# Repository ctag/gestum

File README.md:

# Space Sensei (せんせい)

*Firmware which automatically pairs Bosch SensorTec BNO055 library to any number of sensors and shuttles quaternions to a host computer.*

## Firmware setup

### Serial settings

38400 baud, 8N1

## TLV Packets

TLV (Type-Length-Value-Checksum) is used to minimize data required to send quaternions to host computer.

### Format

* Type - 1 byte opcode (e.g. 0x0C)
* Length - 1 byte unsigned int length of value field.
	* Note - Entire packet is always 'length + 3'
* Value - Raw bytearray.
* Checksum - 1 byte. Validates data integrity.https://68.media.tumblr.com/avatar_ef804b42fa43_128.png
	* Type + Length + [Value1 + Value2 + ValueN] + Checksum = 0x00

### Notes

* Not using preamble/postamble because timeout takes care of synchronization.
	* Timeout is ~30ms. So if comms go down, wait a while and try again.
* Not parsed without length byte.
	* Minimum packet length is 3 bytes.

### Opcodes

Even opcodes are master->mcu. Odd ones are mcu->master.

* 0x02: Heartbeat request (ping)
	* No Value field.
	* Packet: 0x0200FE
* 0x03: Heartbeat response (pong)
	* No Value field.
	* Packet: 0x0300FD
* 0x04: Request System State
	* No Value field.
	* Packet: 0x0400FC
* 0x05: Return System State
	* Value field is 1-2 uint8. 
	* See System state section below.
* 0x06: Request BNO count
	* No Value field.
	* Packet: 0x0600FA
* 0x07: Return BNO count
	* Value field is one uint8
* 0x08: Request BNO Calibration Status
	* Value field is uint8 index of BNO. Must be less than BNO count.
* 0x09: Return BNO Calibration Status
	* Value field is 4 uint8.
	* In order: accel, gyro, mag, sys.
	* Page 48 of datasheet for more.
* 0x0A: Request BNO Quaternion
	* Value field is BNO index.
* 0x0B: Return BNO Quaternion
	* Value field is quaternion. 4 bytes.
* 0xAA: Generic system error
* 0xAB: Generic system error
* 0xAC: Checksum error
* 0xAD: Checksum error
* 0xAE: Timeout with partial packet
* 0xAF: Timeout with partial packet

### System state

Sent as a uint8. Constructed such that any nonzero number indicates a problem (except bootup, which just means wait a bit).

* 0 - Everything's good
* 1 - Bootup (everything's still good)
* 2 - No BNOs detected during scan. Connect them and reboot system.
* 3 - Error initializing BNO. Cycle power to system. Should send erroneous BNO #.

## BNO055

We're using Bosch's BNO055 9-axis fusion IMU. It kinda sucks, and looks like this:

It has a [datasheet](doc/datasheet.pdf), and [C microcontroller library](https://github.com/BoschSensortec/BNO055_driver), with a [3rd party guide](doc/IntegrateBNO055.pdf) to help you integrate the library to your project.

### Bootup

On boot the BNO automatically falls into calibration mode. The space sensei firmware will wait until the minimum (maybe) calibration is met. Then it will proceed to normal operation.

On the debugging hardware, an LED is yellow during calibration, then switches to green for normal operation.

For NDEF mode (which we're using) the most basic calibration required is magnotometer (rotate sensor 360 like a compass).

### Calibration

Also listed in BNO datasheet page 47. Reiterated here for convenience.

* Mag
	* Rotate sensor in a circle like a compass.
* Gyro
	* Place sensor in a stable position for a few seconds.
* Accel
	* Place the device in 6 different stable positions for a period of few seconds to allow the
accelerometer to calibrate.
	* Make sure that there is slow movement between 2 stable positions
	* The 6 stable positions could be in any direction, but make sure that the device is lying at
least once perpendicular to the x, y and z axis.

Calibration status (as returned by command) is 0-3 for each with 0 being uncalibrated and 3 being nicely calibrated.

## Timing

Atmega328 runs at 16,000,000Hz. 0.000000063 seconds per tick.

BNO supposedly runs in NDEF mode at 100Hz. Haven't determined if it can be polled faster than this but with only 100Hz worth of valid data.

Esp8266 runs at a hair faster than the 4th order element of the Laplace transform of the function which defines cumulative average lava flow rates in North America but only up to the 19th century. Which is to say it actually runs at 80Mhz but has a lot of firmware cruft and I have no idea if that's a net positive or not.

## ESP8266

[notes here](esp/esp.md)

## Dev Notes

* 3 BNOs + TCA mux is right at the edge of the max power draw for my ftdi cable..
* Dupont/header connections make i2c unreliable. For implementation either solder connections or remove any stress/movement in wire connections.
* Firmware startup has a ~1 second delay which allows BNOs to boot. Is mentioned in the BNO datasheet.

## To Do  

Explain checksumming

Add quaternion member byte order in return tlv

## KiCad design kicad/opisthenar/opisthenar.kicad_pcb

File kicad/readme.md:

# KiCAD

These files contain the PCB designs for space sensei.

## Opisthenar

Opisthenar is the back of the hand, where we intend to mount the central processing and communication elements of this sensor network.

## Phalanx

Phalanges are the bone segments in fingers, where we intend to mount the individual BNO055 sensors that report back to the Opisthenar PCB.

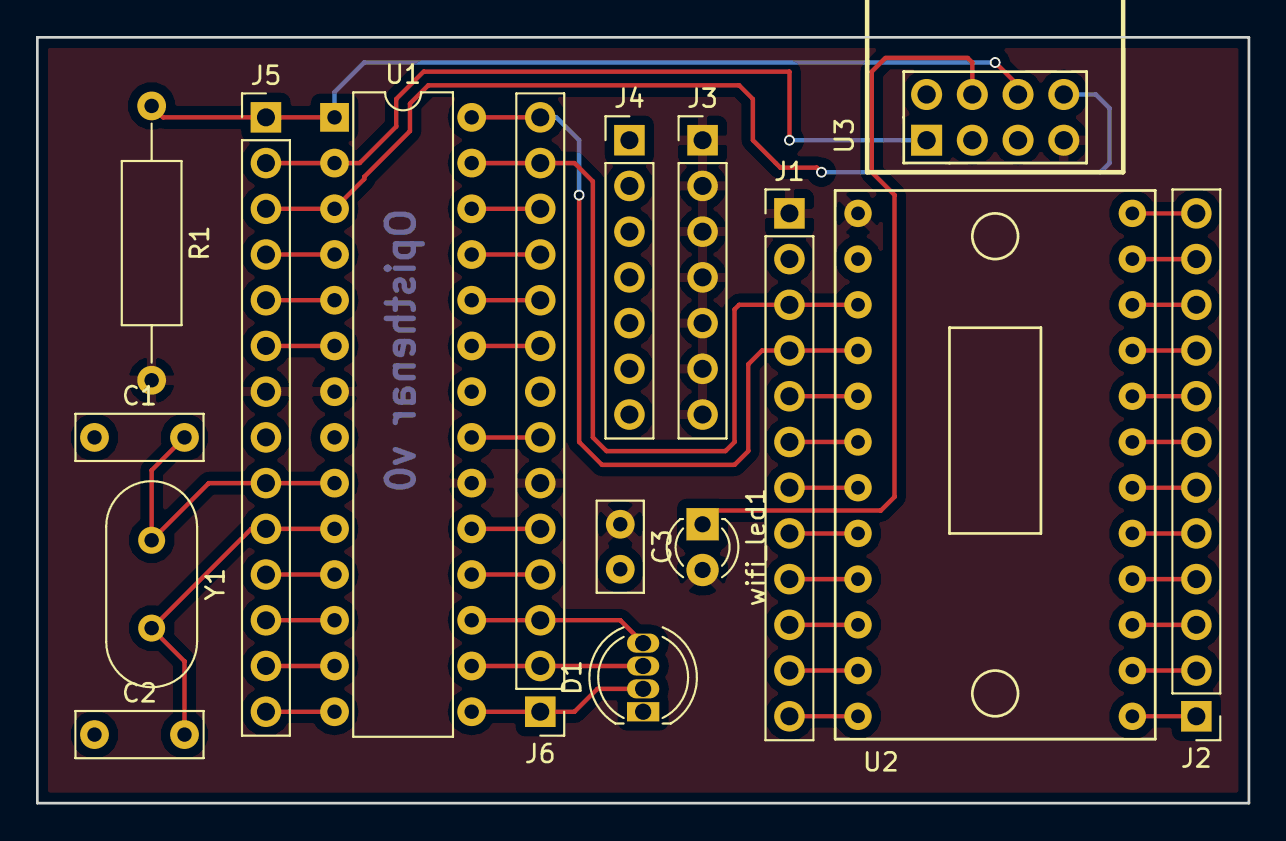
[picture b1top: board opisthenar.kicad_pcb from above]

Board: 2 copper layers, 67.3 x 42.5 mm, 16 parts (0 on the bottom side), 47 nets.

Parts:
C1, C2: 22pF; C_Disc_D7.0mm_W2.5mm_P5.00mm
C3: 10uF; C_Disc_D5.0mm_W2.5mm_P2.50mm
D1: LED_CRGB; LED_D5.0mm-4
J1, J2: CONN_01X12; Pin_Header_Straight_1x12_Pitch2.54mm
J3, J4: CONN_01X07; Pin_Header_Straight_1x07_Pitch2.54mm
J5, J6: CONN_01X14; Pin_Header_Straight_1x14_Pitch2.54mm
R1: 10K; R_Axial_DIN0309_L9.0mm_D3.2mm_P15.24mm_Horizontal
U1: ATMEGA328P-PU; DIP-28_W7.62mm
U2: TCA9548A_ADAFRUIT
U3: ESP-01v090; ESP-01
Y1: 16MHz Crystal; Crystal_HC49-4H_Vertical
wifi_led1: LED; LED_D3.0mm

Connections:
/AREF: J6.7, U1.21
/BLUE: D1.4, J6.3, U1.17
/GREEN: D1.3, J6.2, U1.16
/PB0: J5.14, U1.14
/PB4: J6.4, U1.18
/PB5: J6.5, U1.19
/PC0: J6.9, U1.23
/PC1: J6.10, U1.24
/PC2: J6.11, U1.25
/PC3: J6.12, U1.26
/PD2: J5.4, U1.4
/PD3: J5.5, U1.5
/PD4: J5.6, U1.6
/PD5: J5.11, U1.11
/PD6: J5.12, U1.12
/PD7: J5.13, U1.13
/RED: D1.2, J6.1, U1.15
/RX: J5.2, U1.2, U3.1
/SC0: J1.10, U2.10
/SC1: J1.12, U2.12
/SC2: J2.2, U2.14
/SC3: J2.4, U2.16
/SC4: J2.6, U2.18
/SC5: J2.8, U2.20
/SC6: J2.10, U2.22
/SC7: J2.12, U2.24
/SCL: J1.4, J6.14, U1.28, U2.4
/SD0: J1.9, U2.9
/SD1: J1.11, U2.11
/SD2: J2.1, U2.13
/SD3: J2.3, U2.15
/SD4: J2.5, U2.17
/SD5: J2.7, U2.19
/SD6: J2.9, U2.21
/SD7: J2.11, U2.23
/SDA: J1.3, J6.13, U1.27, U2.3
/TCA_A0: J1.6, U2.6
/TCA_A1: J1.7, U2.7
/TCA_A2: J1.8, U2.8
/TX: J5.3, U1.3, U3.8
/XTAL1: C1.2, J5.9, U1.9, Y1.1
/XTAL2: C2.2, J5.10, U1.10, Y1.2
/~RESET: J5.1, R1.1, U1.1, U3.6
/~TCA_RESET: J1.5, U2.5
GND: C1.1, C2.1, C3.2, D1.1, J1.2, J4.1, J4.2, J4.3, J4.4, J4.5, J4.6, J4.7, J5.8, J6.8, U1.8, U1.22, U2.2, U3.2
unnamed: U3.4, wifi_led1.1
VCC: C3.1, J1.1, J3.1, J3.2, J3.3, J3.4, J3.5, J3.6, J3.7, J5.7, J6.6, R1.2, U1.7, U1.20, U2.1, U3.7, wifi_led1.2

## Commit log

2017-02-02 Framework, codeblocks project.
2017-02-02 Brought in i2c library
2017-02-02 Tied in i2c functions.
2017-02-02 printf support.
2017-02-10 rectangular integration approximation
2017-02-10 plot 1
2017-02-10 interrupt driven timing.
2017-02-10 Hold for calibration on boot
2017-02-10 Cleaned up setup().
2017-02-10 Trapezoidal integration, arithmetic fix, and lowpass filtering.
2017-02-10 Fixed error in integration.
2017-05-30 Renamed readme as markdown.
2017-05-30 Removed debugging from usart lib.
2017-05-30 Testing workaround for bno driver.
2017-05-31 Example auto-detect for bno and mux chains.
2017-05-31 Be careful about sporadic behavior caused by current draw.
2017-05-31 Squashed a compiler warning in bno library.
2017-06-02 Updated libraries.
2017-06-02 Example code that scans TCA mux for BNO055s.
2017-06-02 Notes from debugging i2c today.
2017-06-21 linked list
2017-06-21 output timer
2017-06-21 Fixed compiler error for signed char comparison.
2017-06-21 Switched to quaternions.
2017-06-21 updated gitignore.
2017-06-21 Added 3d finger-mount model.
2017-06-21 Project files updated.
2017-06-21 Removed code for euler, timerb, port outputs.
2017-06-26 Added notes about tlv.
2017-06-26 Fixed checksum checker.
2017-06-28 Cleaned up readme and added tlv description.
2017-06-28 retext lags.
2017-06-28 Brought in PDF datasheet and documentation.
2017-06-28 Added bno section to readme.
2017-06-28 Cleaned up global variables.
2017-06-28 Added system state
2017-06-28 Implemented tlv.
2017-06-28 Added tlv notes.
2017-06-29 Added notes to readme after meeting with Nick.
2017-06-29 Set timeout as timerB, removed debugging statements.
2017-06-29 Implemented basic error command.
2017-06-29 More error responses.
2017-06-30 bugfix to return system state.
2017-06-30 Added esp readme.
2017-06-30 Committing esp binaries for convenience.
2017-06-30 Retext is shite.
2017-06-30 Added socat notes for esp-link.
2017-06-30 Again, retext sucks.
2017-06-30 Retext suuuuucks.
2017-06-30 markdown editor backup file.
2017-06-30 Flashing script to uploda firmware over esp-link.
2017-06-30 lengthened tlv timeout to ~50ms to increase catch rate with esp-link
2017-06-30 Added timing notes to readme.
2017-06-30 Added dev notes to esp readme.
2017-07-05 Updated esp readme.
2017-07-05 Don't use this script directly, but it's here anyway.
2017-07-05 Added pinboard PCB for reconfiguration.
2017-07-05 Adding esp-01 docs.
2017-07-05 Added comparison of esp boards.
2017-07-05 typo
2017-07-05 Added another link to flashing.md
2017-07-05 Organizing pcb folder.
2017-07-06 Trying new library management approach.
2017-07-07 Revert "Trying new library management approach."
    This reverts commit 74f6f6aeeaeb2c9e3e0855570cf136f5f7da9f23.
    It didn't work.
2017-07-10 Added some gitignores
2017-07-10 Added TCA to kicad schmatic
2017-07-11 esp led notes.
2017-07-11 Added esp-01 to schematic.
2017-07-12 Updated opisthenar pcb for new pcb run.
2017-07-12 Renders of opisthenar sent to oshpark.
